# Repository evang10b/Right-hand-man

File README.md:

# Right-hand-man
Right hand man is a &-Key macropad with built in LED lights and an Oled display. Its purpose is to make normal shortcut keys related to media much more accesible.

# Features
- 128x32 OLED Display
- EC11 Rotary encode
- 6 SK6812 MINI-E LEDs

# PCB

# Schematic

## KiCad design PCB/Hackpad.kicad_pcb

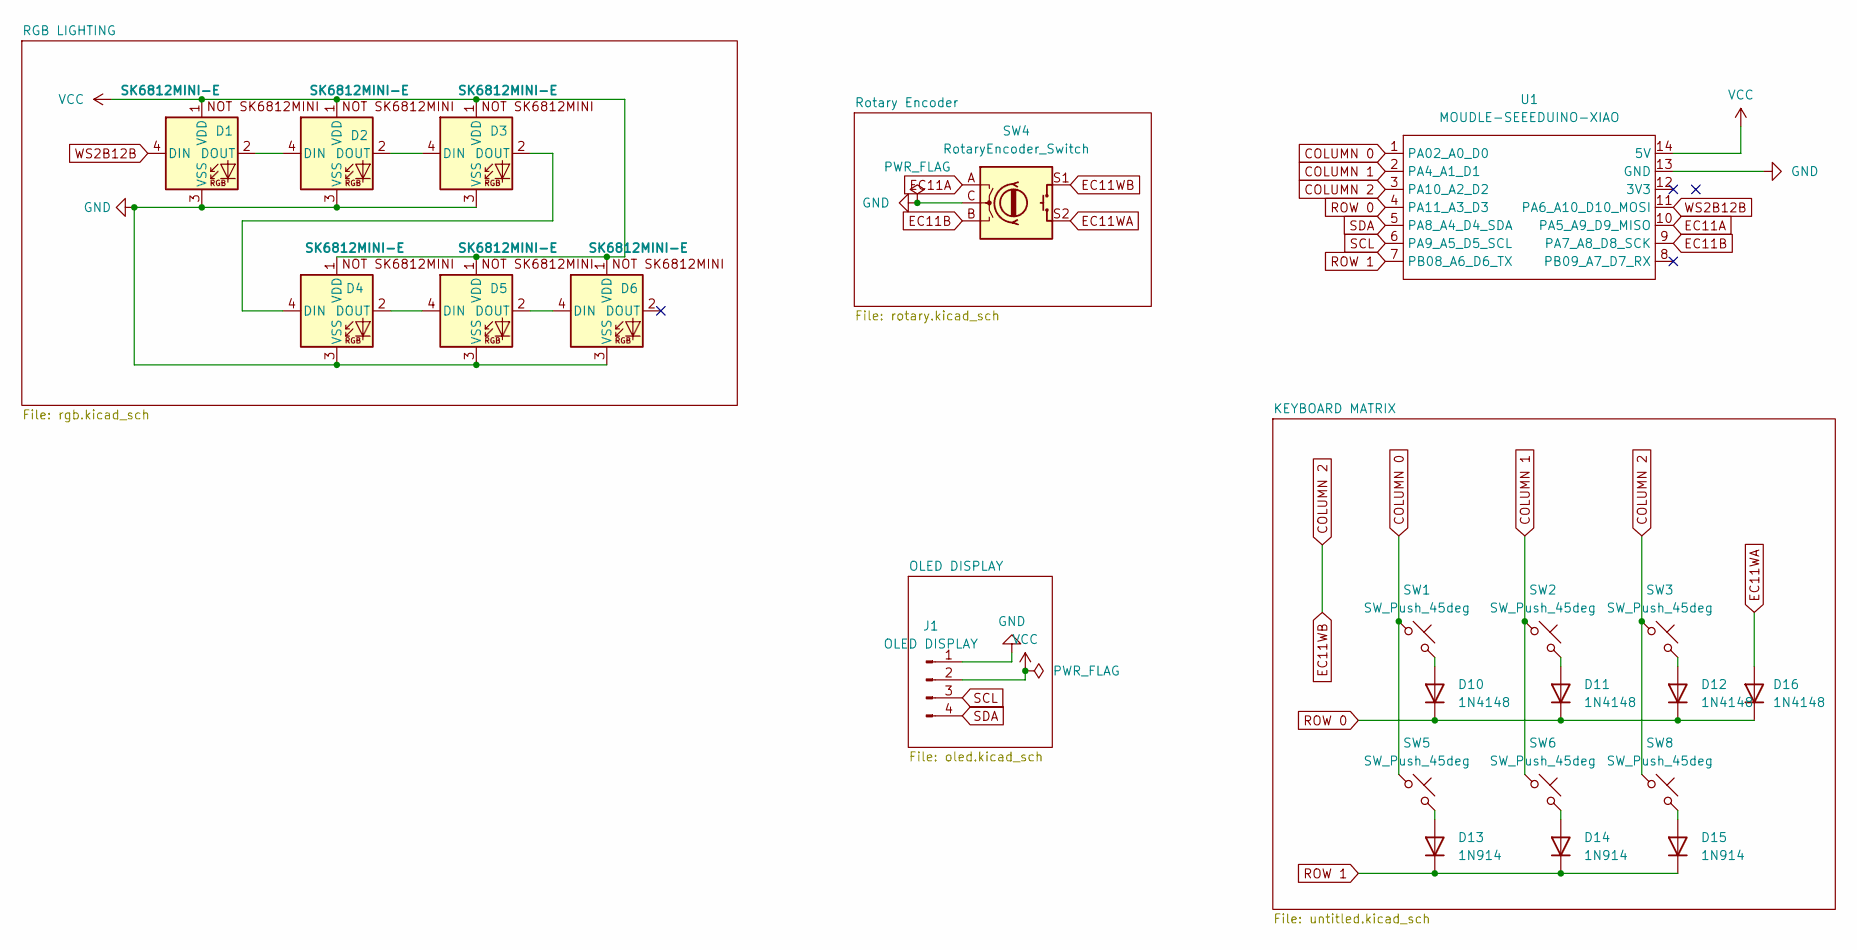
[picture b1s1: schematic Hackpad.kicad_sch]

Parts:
D1, D2, D3, D4, D5, D6: SK6812MINI-E; SK6812MINI-E_fixed
D10, D11, D12, D16: 1N4148; D_DO-35_SOD27_P7.62mm_Horizontal
D13, D14, D15: 1N914; D_DO-35_SOD27_P7.62mm_Horizontal
J1: OLED DISPLAY; PinHeader_1x04_P2.54mm_Vertical
SW1, SW2, SW3, SW5, SW6, SW8: SW_Push_45deg; SW_Cherry_MX_1.00u_PCB
SW4: RotaryEncoder_Switch; RotaryEncoder_Alps_EC11E-Switch_Vertical_H20mm
U1: MOUDLE-SEEEDUINO-XIAO; XIAO-Generic-Hybrid-14P-2.54-21X17.8MM

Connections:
COLUMN 0: SW1.1, SW5.1, U1.1 (PA02_A0_D0)
COLUMN 1: SW2.1, SW6.1, U1.2 (PA4_A1_D1)
COLUMN 2: SW3.1, SW4.S1, SW8.1, U1.3 (PA10_A2_D2)
EC11A: SW4.A, U1.10 (PA5_A9_D9_MISO)
EC11B: SW4.B, U1.9 (PA7_A8_D8_SCK)
EC11WA: D16.2 (A), SW4.S2
GND: D1.3 (VSS), D2.3 (VSS), D3.3 (VSS), D4.3 (VSS), D5.3 (VSS), D6.3 (VSS), J1.1, SW4.C, U1.13 (GND)
unnamed: D1.2 (DOUT), D2.4 (DIN)
unnamed: D2.2 (DOUT), D3.4 (DIN)
unnamed: D3.2 (DOUT), D4.4 (DIN)
unnamed: D4.2 (DOUT), D5.4 (DIN)
unnamed: D5.2 (DOUT), D6.4 (DIN)
unnamed: D10.2 (A), SW1.2
unnamed: D11.2 (A), SW2.2
unnamed: D12.2 (A), SW3.2
unnamed: D13.2 (A), SW5.2
unnamed: D14.2 (A), SW6.2
unnamed: D15.2 (A), SW8.2
ROW 0: D10.1 (K), D11.1 (K), D12.1 (K), D16.1 (K), U1.4 (PA11_A3_D3)
ROW 1: D13.1 (K), D14.1 (K), D15.1 (K), U1.7 (PB08_A6_D6_TX)
SCL: J1.3, U1.6 (PA9_A5_D5_SCL)
SDA: J1.4, U1.5 (PA8_A4_D4_SDA)
VCC: D1.1 (VDD), D2.1 (VDD), D3.1 (VDD), D4.1 (VDD), D5.1 (VDD), D6.1 (VDD), J1.2, U1.14 (5V)
WS2B12B: D1.4 (DIN), U1.11 (PA6_A10_D10_MOSI)

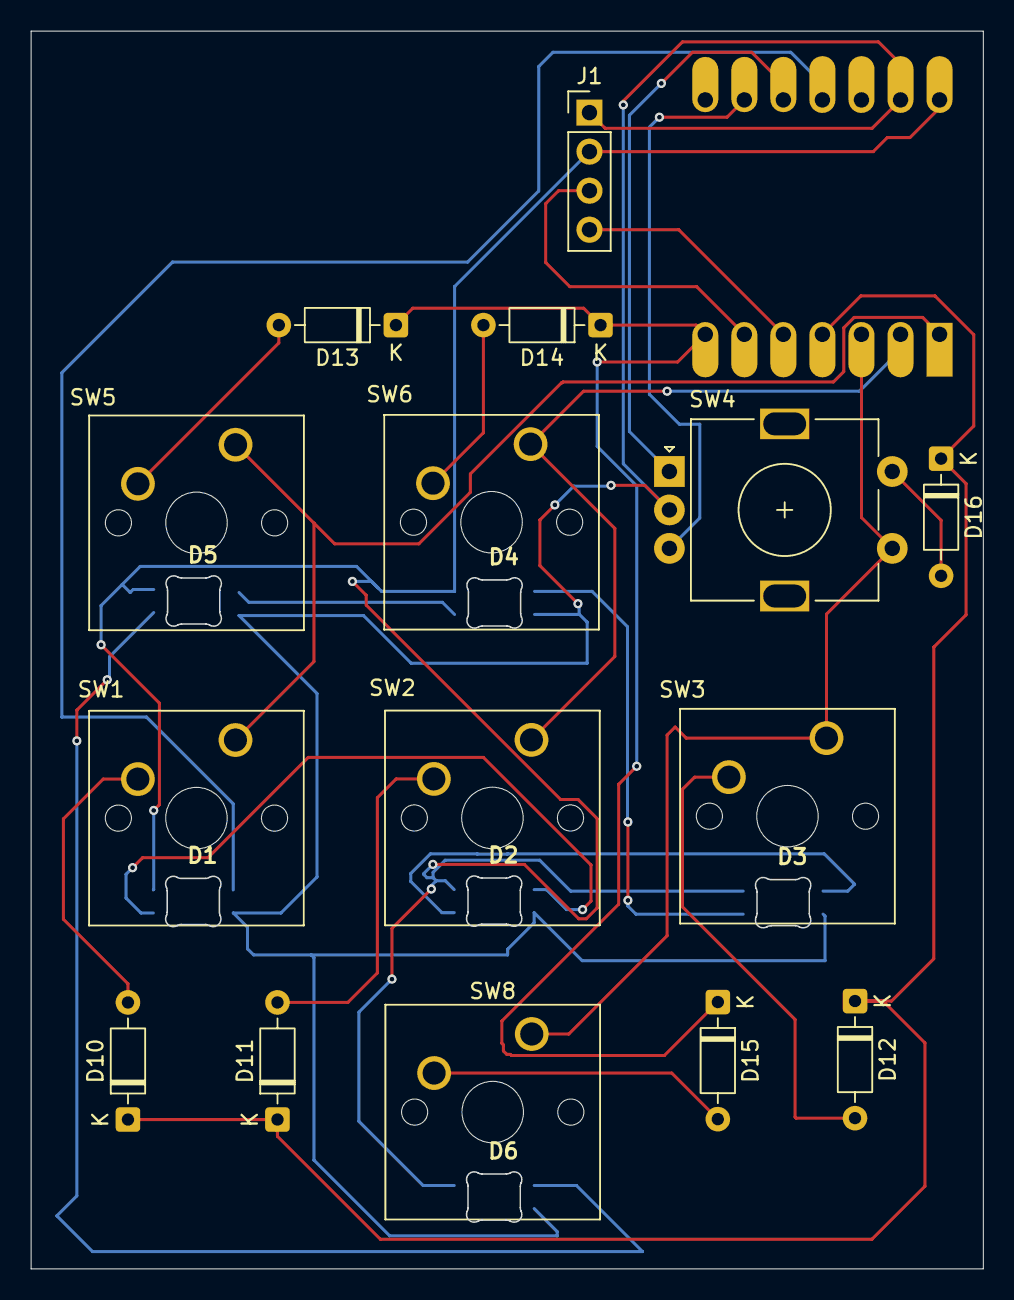
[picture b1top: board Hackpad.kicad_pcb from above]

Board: 2 copper layers, 61.9 x 80.5 mm, 22 parts (1 on the bottom side), 24 nets.
